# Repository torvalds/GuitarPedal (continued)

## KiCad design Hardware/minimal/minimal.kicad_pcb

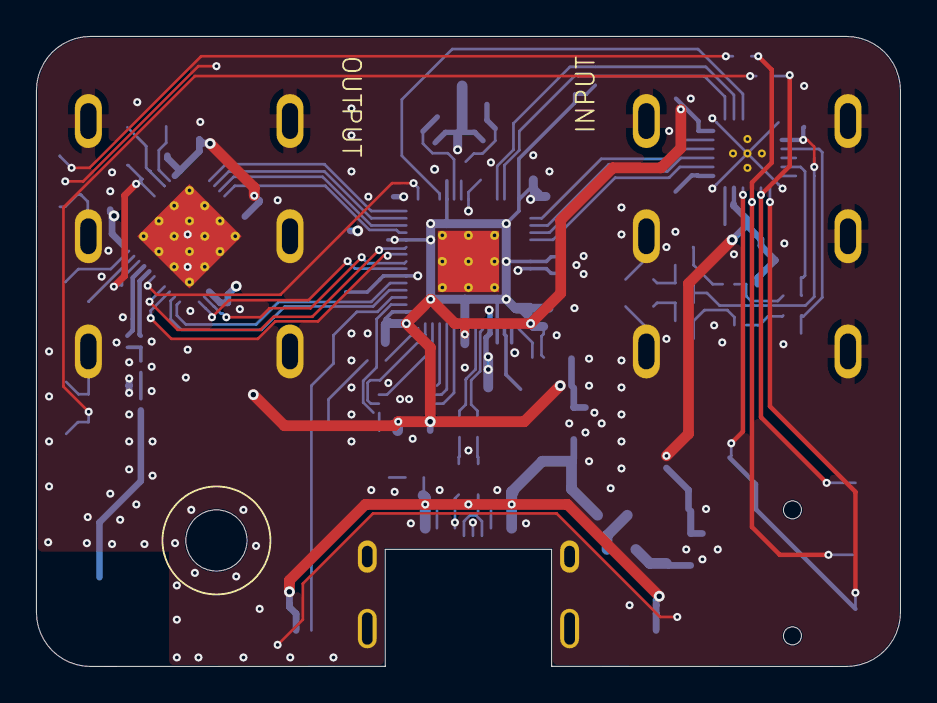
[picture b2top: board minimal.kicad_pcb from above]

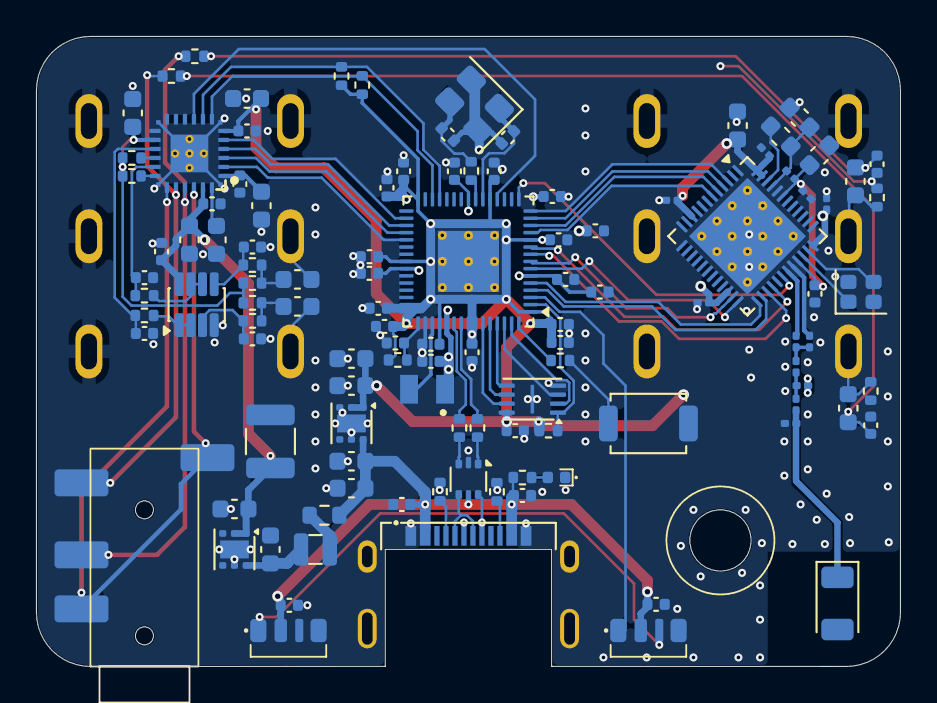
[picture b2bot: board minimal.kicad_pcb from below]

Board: 4 copper layers, 48.0 x 35.0 mm, 114 parts (112 on the bottom side), 80 nets.

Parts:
AE501: 2.4GHz; Johanson_2450AT18x100
C102, C103, C107, C108, C301, C320, C322, C323, C404, C405, C407, C408, C409, C410, C411, C412, C413, C415, C417: 0.1uF; C_0402_1005Metric
C104, C106, C109, C110, C111, C112, C303, C304, C305, C309, C318, C319, C509, C510: 2.2uF; C_0603_1608Metric
C105: 22uF; C_1210_3225Metric
C302, C308, C310, C311, C511: 2.2nF; C_0402_1005Metric
C306, C307: 150pF; C_0402_1005Metric
C316, C317, C321, C508: 10uF; C_0603_1608Metric
C401, C402, C403, C406, C414, C416, C418, C421, C422: 4.7uF; C_0402_1005Metric
C419, C420: 15pF; C_0402_1005Metric
C501: 1.5pF; C_0201_0603Metric
C502: 2.0pF; C_0201_0603Metric
C503: 0.3pF; C_0201_0603Metric
C504, C505, C506, C507: 0.1uF; C_0201_0603Metric
C512: 10nF; C_0201_0603Metric
D101: LED; LED_0402_1005Metric
D102, D103: WS2812B-4020-V6
FB501: 120Ω; L_0201_0603Metric
J101: USB_C_Receptacle_USB2.0_16P; TYPE-C-16P-CB1.6
J301, J302: AudioJack3_SwitchTR; NRJ6HM-1-PRE
J303: AudioJack4; PJ-320D
L101: 2.2uH; L_0806
L401: 3.3uH; AOTA-B2016
L501: 4.7uH; L_0603_1608Metric
L502: 2.7nH; L_0201_0603Metric
L503, L504: 3.5nH; L_0201_0603Metric
R101, R102, R105, R106: 5k1; R_0402_1005Metric
R103, R401, R403: 2.2kΩ; R_0402_1005Metric
R104: 1R; R_0603_1608Metric
R301, R307: 1k; R_0402_1005Metric
R302, R303, R304, R308: 1MEG; R_0402_1005Metric
R305, R306, R309, R310, R312, R313: 100R; R_0402_1005Metric
R402, R404, R405: 33Ω; R_0402_1005Metric
R406: 1kΩ; R_0402_1005Metric
SW101: SW_SPST; SW_SPST_TS-1088-xR020
U102: USBLC6-2P6; SOT-666
U103, U104: TLV76733DRVx; WSON-6-1EP_2x2mm_P0.65mm_EP1x1.6mm
U301: OPA2323; TSOT-23-8
U302: TAC5112; TAC5242
U401: APS6404L-3SQRx-ZR; Winbond_USON-8-1EP_3x2mm_P0.5mm_EP0.2x1.6mm
U402: RP2354A; QFN-60-1EP_7x7mm_P0.4mm_EP3.4x3.4mm_ThermalVias
U501: NRF54L10-QFAA-R7; QFN-48-1EP_6x6mm_P0.4mm_EP4.6x4.6mm_ThermalVias
Y401: ABM8-272-T3; Crystal_SMD_3225-4Pin_3.2x2.5mm
Y501: 32MHz; Crystal_SMD_2016-4Pin_2.0x1.6mm

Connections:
+1V1: C402.1, C403.1, C405.1, C407.1, C408.1, L401.1, U402.6 (DVDD), U402.23 (DVDD), U402.39 (DVDD), U402.50 (VREG_FB)
+3.3VA: C105.1, C109.1, C301.2, C321.1, C323.1, U103.1 (OUT), U103.2 (SNS), U301.8 (V+), U302.23 (AVDD)
+3V3: C111.1, C112.1, C316.1, C322.1, C401.1, C404.1, C409.1, C410.1, C411.1, C412.1, C413.1, C414.1, C415.1, C416.1, C417.1, C418.1, C421.1, C422.1, C504.1, C505.1, C506.1, C507.1, C508.1, R105.1, R106.1, R401.2, R402.1, U104.1 (OUT), U104.2 (SNS), U302.6 (IOVDD), U401.8 (VDD), U402.1 (IOVDD), U402.11 (IOVDD), U402.20 (IOVDD), U402.30 (IOVDD), U402.38 (IOVDD), U402.44 (ADC_AVDD), U402.45 (IOVDD), U402.49 (VREG_VIN), U402.53 (USB_OTP_VDD), U402.54 (QSPI_IOVDD), U501.10 (VDD), U501.22 (VDD), U501.36 (VDD), U501.47 (VDD), U501.48 (VDD)
/BOOTSEL: R403.1, SW101.2 (B)
/OUT1P: J303.T, R301.1, U302.20 (OUT1P)
/OUT2P: J303.R1, R307.1, U302.21 (OUT2P)
/RP2354/GPIO0: R401.1, U401.1 (~CE), U402.2 (GPIO0)
/RP2354/GPIO1: D102.1 (DIN), U402.3 (GPIO1)
/RP2354/GPIO2: U402.4 (GPIO2), U501.26 (SWDCLK)
/RP2354/GPIO3: U402.5 (GPIO3), U501.25 (SWDIO)
/RP2354/GPIO4: U402.7 (GPIO4), U501.24 (P0.01)
/RP2354/GPIO5: U402.8 (GPIO5), U501.23 (P0.00)
/RP2354/GPIO6: U402.9 (GPIO6), U501.27 (P0.02)
/RP2354/GPIO7: U402.10 (GPIO7), U501.28 (P0.03)
/RP2354/GPIO8: U402.12 (GPIO8), U501.6 (P1.05/AIN1)
/RP2354/GPIO9: U402.13 (GPIO9), U501.5 (P1.04/AIN0)
/RP2354/GPIO10: U402.14 (GPIO10), U501.4 (P1.03/NFC2/CK)
/RP2354/GPIO11: U402.15 (GPIO11), U501.3 (P1.02/NFC1)
/RP2354/GPIO12: U402.16 (GPIO12), U501.30 (nRESET)
/RP2354/GPIO15: U302.9 (GPIO1), U402.19 (GPIO15)
/RP2354/GPIO16: R106.2, U302.8 (SDA), U402.27 (GPIO16)
/RP2354/GPIO17: R105.2, U302.7 (SCL), U402.28 (GPIO17)
/RP2354/GPIO20: U302.5 (DIN), U402.32 (GPIO20)
/RP2354/GPIO21: U302.4 (DOUT), U402.33 (GPIO21)
/RP2354/GPIO22: U302.3 (FSYNC), U402.34 (GPIO22)
/RP2354/GPIO23: U302.2 (BCLK), U402.35 (GPIO23)
/RP2354/SCLK: U401.6 (SCLK), U402.56 (QSPI_SCLK)
/RP2354/SD0: U401.5 (SI/SIO0), U402.57 (QSPI_SD0)
/RP2354/SD1: U401.2 (SO/SIO1), U402.59 (QSPI_SD1)
/RP2354/SD2: U401.3 (SIO2), U402.58 (QSPI_SD2)
/RP2354/SD3: U401.7 (SIO3), U402.55 (QSPI_SD3)
/RP2354/VREG_AVDD: C406.1, R402.2, U402.46 (VREG_AVDD)
/RP2354/VREG_LX: L401.2, U402.48 (VREG_LX)
/RP2354/XIN: C419.1, U402.21 (XIN), Y401.1
/RP2354/XOUT: R406.1, U402.22 (XOUT)
/TAC5212/DREG: C317.1, C320.1, U302.1 (DREG)
/TAC5212/IN1M: R313.2, U302.16 (IN1M)
/TAC5212/IN1P: C310.2, R309.2, U302.15 (IN1P)
/TAC5212/IN2M: R312.2, U302.18 (IN2M)
/TAC5212/IN2P: C311.2, R310.2, U302.17 (IN2P)
/TAC5212/IN^{LEFT}: C303.1, J301.T
/TAC5212/IN^{RIGHT}: C304.1, J301.R
/TAC5212/MICBIAS: C319.1, R303.1, R304.2, R312.1, R313.1, U302.14 (MICBIAS)
/TAC5212/OUT1M: J303.R2, J303.S, U302.19 (OUT1M), U302.22 (OUT2M)
/TAC5212/OUT^{LEFT}: C305.2, J302.T, R302.1
/TAC5212/OUT^{RIGHT}: C309.2, J302.R, R308.1
/TAC5212/VREF: C318.1, U302.24 (VREF)
/USB-D+: R404.2, U102.1 (I/O1)
/USB-D-: R405.2, U102.3 (I/O2)
/USBCONN-D+: J101.A6 (D+), J101.B6 (D+), U102.6 (I/O1)
/USBCONN-D-: J101.A7 (D-), J101.B7 (D-), U102.4 (I/O2)
/nRF54L10/DECA: C510.1, C511.1, C512.1, FB501.2, U501.33 (DECRF), U501.43 (DECA)
/nRF54L10/DECD: C509.1, FB501.1, L501.1, U501.45 (DECD)
GND: C102.1, C103.1, C104.2, C105.2, C106.2, C107.1, C108.1, C109.2, C110.2, C111.2, C112.2, C301.1, C302.1, C306.2, C307.2, C308.1, C310.1, C311.1, C316.2, C317.2, C318.2, C319.2, C320.2, C321.2, C322.2, C323.2, C401.2, C402.2, C403.2, C404.2, C405.2, C406.2, C407.2, C408.2, C409.2, C410.2, C411.2, C412.2, C413.2, C414.2, C415.2, C416.2, C417.2, C418.2, C419.2, C420.2, C421.2, C422.2, C501.2, C502.2, C503.2, C504.2, C505.2, C506.2, C507.2, C508.2, C509.2, C510.2, C511.2, C512.2, D101.1 (K), D102.4 (VSS), D103.4 (VSS), J101.A1 (GND), J101.A12 (GND), J101.B1 (GND), J101.B12 (GND), J101.SH (SHIELD), J301.RN, J301.S, J301.TN, J302.S, R101.2, R102.2, R302.2, R308.2, SW101.1 (A), U102.2 (GND), U103.3 (GND), U103.5 (GND), U103.7 (PAD), U104.3 (GND), U104.5 (GND), U104.7 (PAD), U301.4 (V-), U302.13 (ADDR), U302.A1 (GND), U302.A2 (GND), U302.A3 (GND), U302.A4 (GND), U302.PAD (GND), U401.4 (VSS), U401.9 (EPAD), U402.47 (VREG_PGND), U402.61 (GND), U501.32 (VSS_PA), U501.44 (VSS), U501.49 (VSS/PAD), Y401.2 (G), Y401.4 (G), Y501.2 (G), Y501.4 (G)
unnamed: AE501.1 (FEED_1), C503.1, L504.1
unnamed: C302.2, C305.1, R301.2
unnamed: C303.2, R303.2, R305.1
unnamed: C304.2, R304.1, R306.1
unnamed: C308.2, C309.1, R307.2
unnamed: C420.1, R406.2, Y401.3
unnamed: C501.1, L502.1, L503.2
unnamed: C502.1, L503.1, L504.2
unnamed: D101.2 (A), R103.1
unnamed: D102.3 (DOUT), D103.1 (DIN)
unnamed: J101.A5 (CC1), R101.1
unnamed: J101.B5 (CC2), R102.1
unnamed: L101.1, R104.2
unnamed: C106.1, L101.2, U103.6 (IN)
unnamed: C306.1, R305.2, U301.3 (+)
unnamed: R309.1, U301.1, U301.2 (-)
unnamed: C307.1, R306.2, U301.5 (+)
unnamed: R310.1, U301.6 (-), U301.7
unnamed: R403.2, U402.60 (QSPI_SS)
unnamed: R405.1, U402.51 (USB_DM)
unnamed: R404.1, U402.52 (USB_DP)
unnamed: L502.2, U501.31 (ANT)
unnamed: L501.2, U501.46 (DCC)
unnamed: U501.34 (XC1), Y501.1
unnamed: U501.35 (XC2), Y501.3
VBUS: C102.2, C103.2, C104.1, C107.2, C108.2, C110.1, D102.2 (VDD), D103.2 (VDD), J101.A4 (VBUS), J101.A9 (VBUS), J101.B4 (VBUS), J101.B9 (VBUS), R103.2, R104.1, U102.5 (VBUS), U104.6 (IN)

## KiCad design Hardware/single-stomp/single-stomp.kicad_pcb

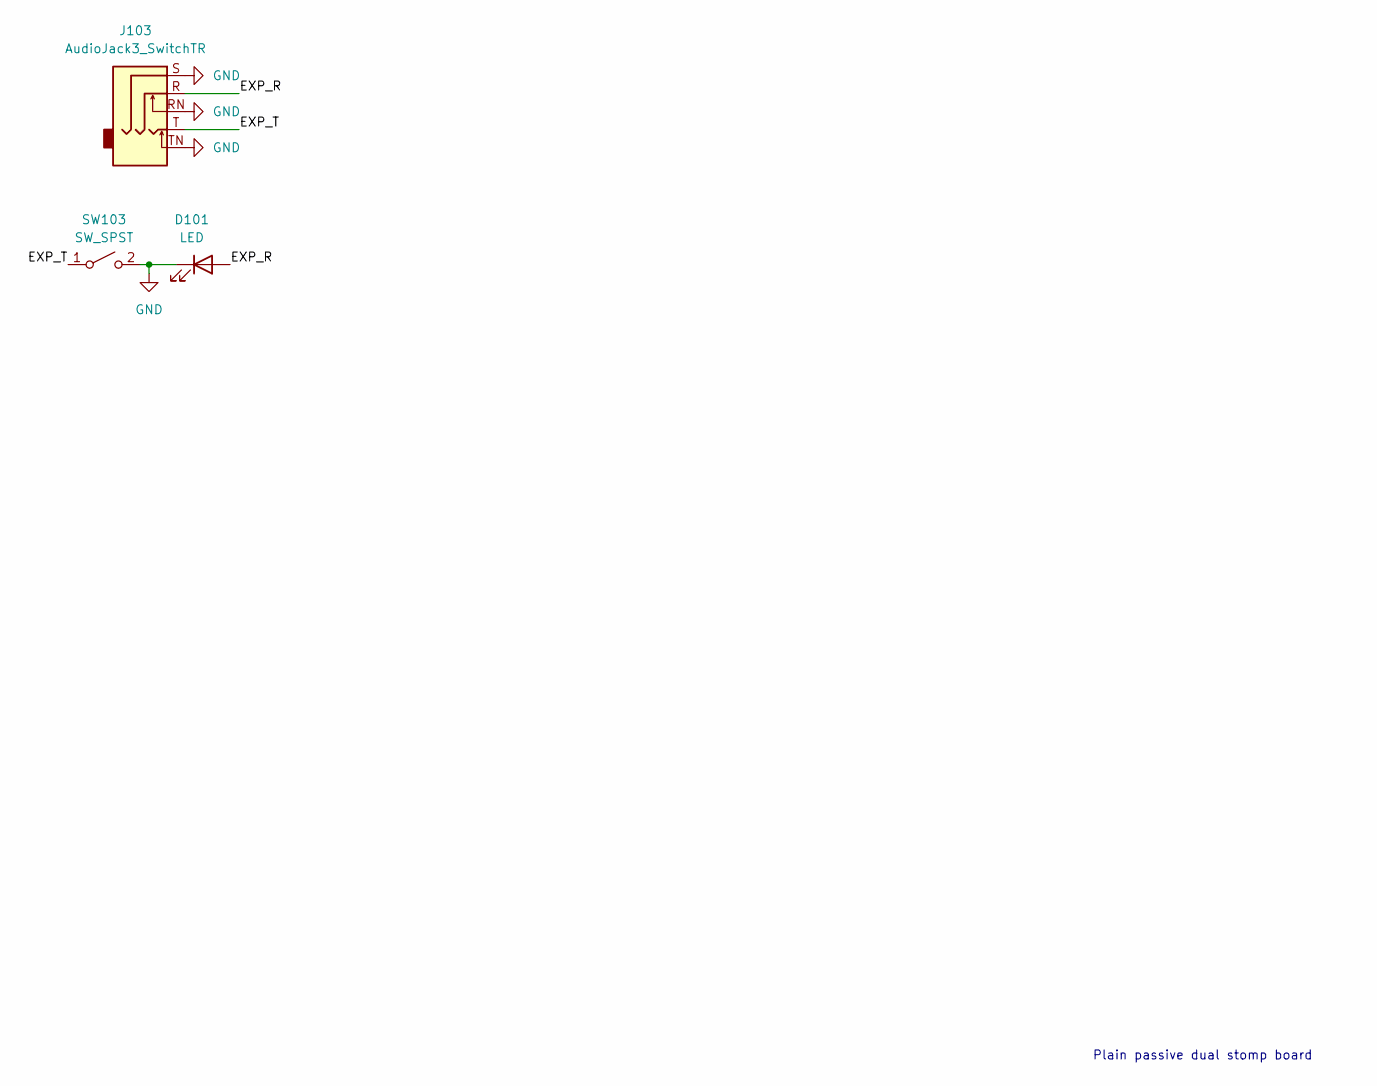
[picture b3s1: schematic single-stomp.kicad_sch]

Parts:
D101: LED; LED_D5.0mm
J103: AudioJack3_SwitchTR; NRJ6HM-1-PRE
SW103: SW_SPST; Daier PBS-24B-2

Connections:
/EXP_R: D101.2 (A), J103.R
/EXP_T: J103.T, SW103.1 (A)
GND: D101.1 (K), J103.RN, J103.S, J103.TN, SW103.2 (B)

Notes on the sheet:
Plain passive dual stomp board

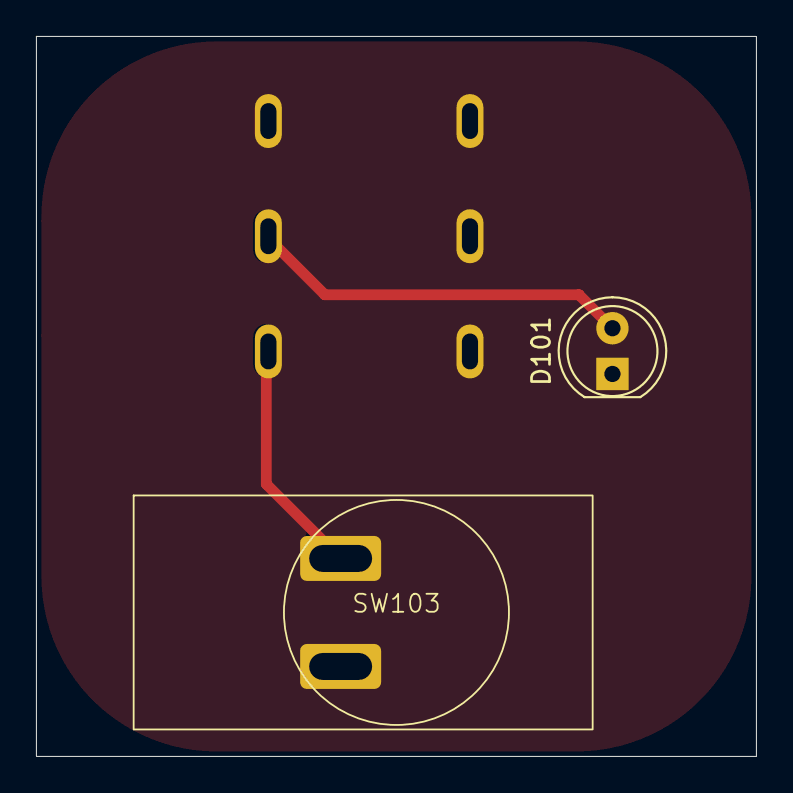
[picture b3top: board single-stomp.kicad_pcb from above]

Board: 2 copper layers, 40.0 x 40.0 mm, 3 parts (0 on the bottom side), 3 nets.

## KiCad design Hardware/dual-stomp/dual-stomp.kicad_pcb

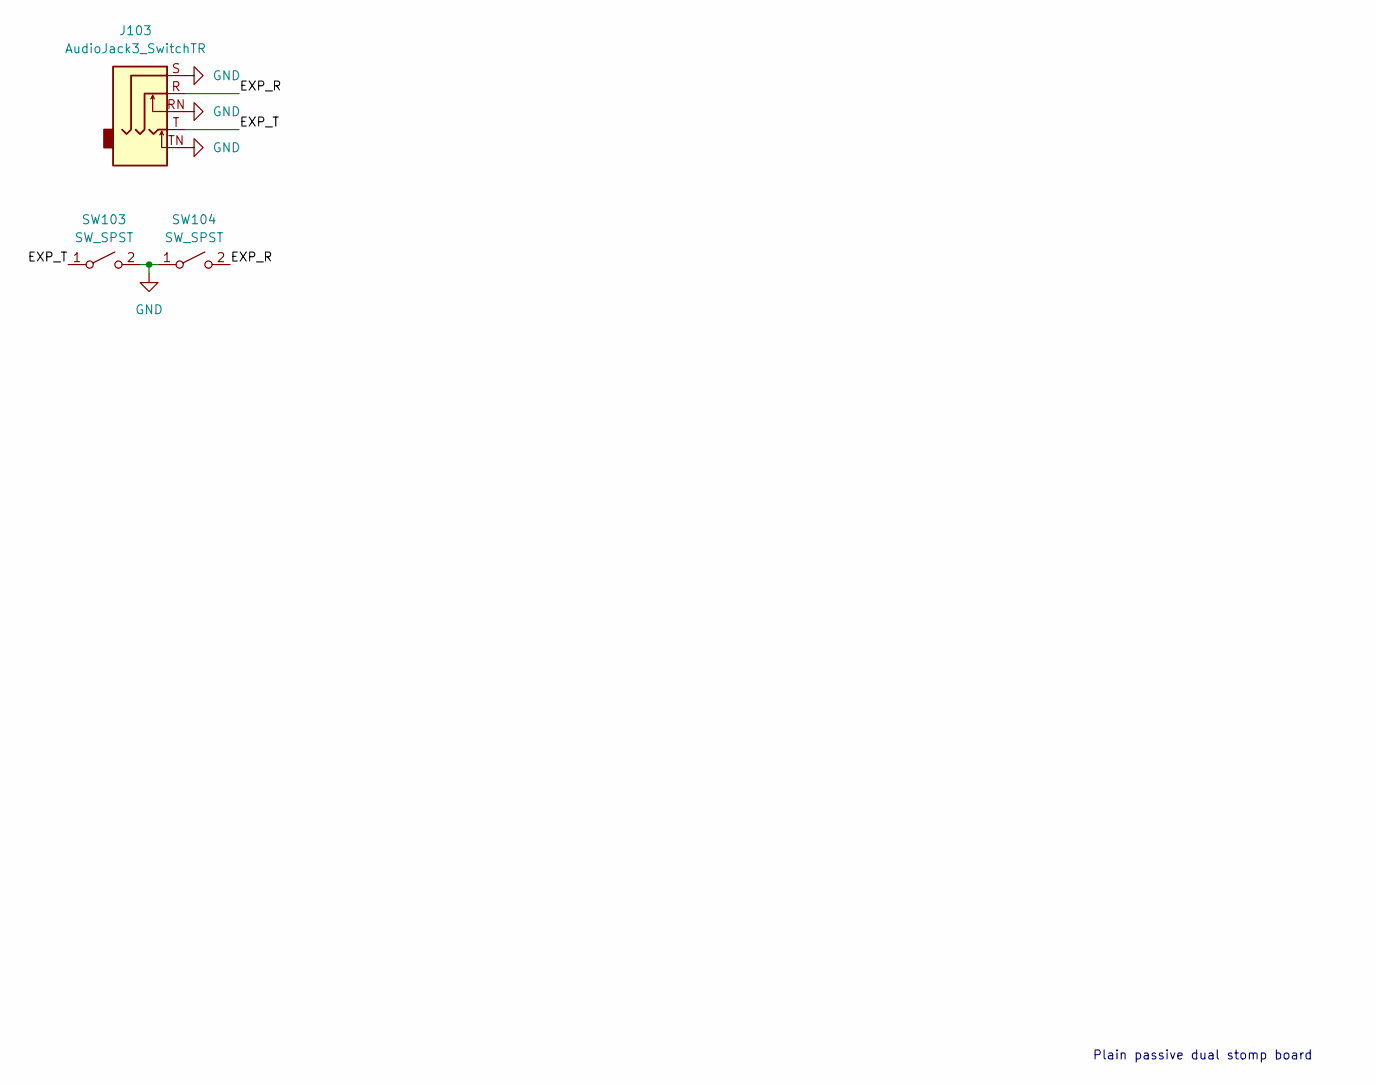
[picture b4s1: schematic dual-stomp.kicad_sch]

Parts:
J103: AudioJack3_SwitchTR; NRJ6HM-1-PRE
SW103, SW104: SW_SPST; Daier PBS-24B-2

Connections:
/EXP_R: J103.R, SW104.2 (B)
/EXP_T: J103.T, SW103.1 (A)
GND: J103.RN, J103.S, J103.TN, SW103.2 (B), SW104.1 (A)

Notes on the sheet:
Plain passive dual stomp board

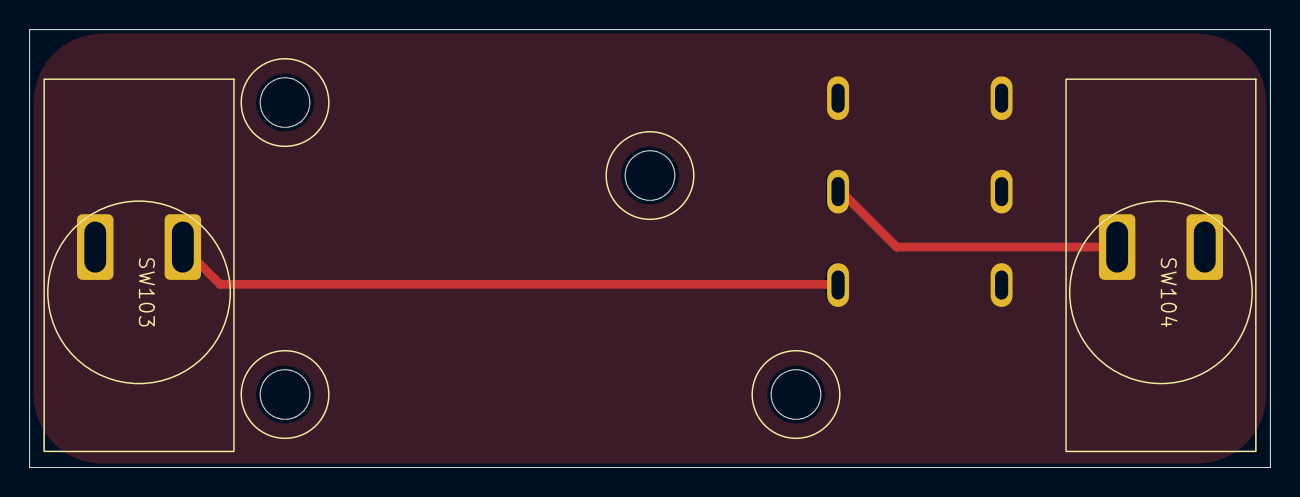
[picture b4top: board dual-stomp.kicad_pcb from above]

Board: 2 copper layers, 85.0 x 30.0 mm, 3 parts (0 on the bottom side), 3 nets.

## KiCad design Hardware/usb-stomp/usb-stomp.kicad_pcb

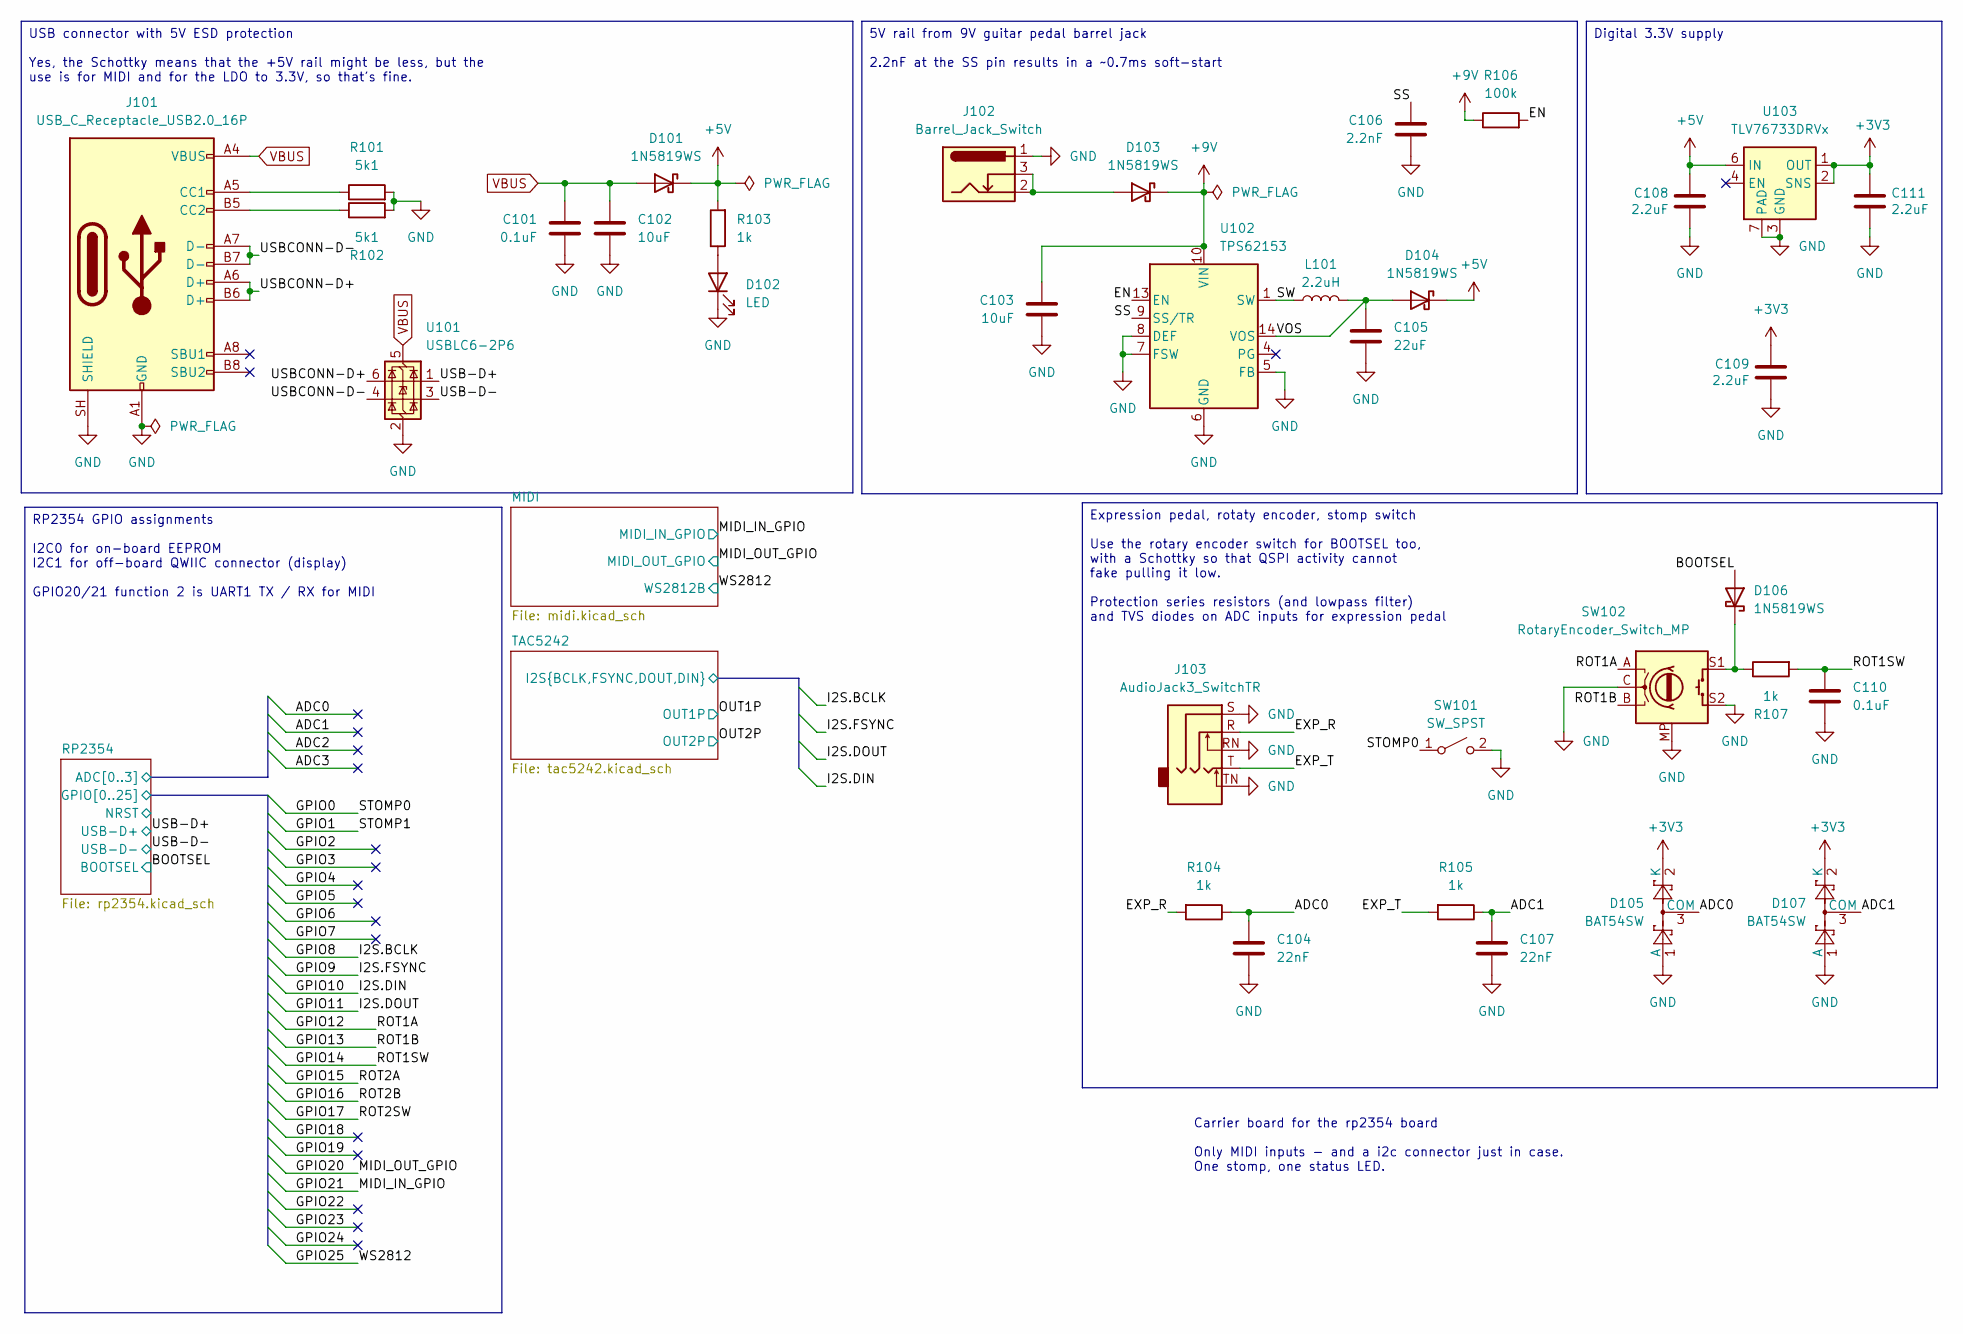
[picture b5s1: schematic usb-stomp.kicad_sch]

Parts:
C101, C110: 0.1uF; C_0402_1005Metric; MANUFACTURER_PART_NUMBER CL05B104KO5NNNC; LCSC PN C1525
C102, C103: 10uF; C_0603_1608Metric; MANUFACTURER_PART_NUMBER GRM188R61E106MA73D; LCSC PN C91606
C104, C107: 22nF; C_0402_1005Metric; MANUFACTURER_PART_NUMBER 0402B223K500NT; LCSC PN C1532
C105: 22uF; C_1210_3225Metric; MANUFACTURER_PART_NUMBER CL32B226KAJNNNE; LCSC PN C309062
C106: 2.2nF; C_0402_1005Metric; MANUFACTURER_PART_NUMBER GRM1555C1H222GA01D; LCSC PN C2987940
C108, C109, C111: 2.2uF; C_0603_1608Metric; MANUFACTURER_PART_NUMBER GRM188Z71E225KE43D; LCSC PN C415535
D101, D103, D104, D106: 1N5819WS; D_SOD-323; MANUFACTURER_PART_NUMBER 1N5819WS; LCSC PN C191023
D102: LED; LED_0402_1005Metric; MANUFACTURER_PART_NUMBER LTST-C281KGKT; LCSC PN C160479
D105, D107: BAT54SW; SOT-323_SC-70; MANUFACTURER_PART_NUMBER BAT54SW; LCSC PN C22466373
J101: USB_C_Receptacle_USB2.0_16P; USB_C_Receptacle_GCT_USB4105-xx-A_16P_TopMnt_Horizontal; MANUFACTURER_PART_NUMBER GT-USB-7010C; LCSC PN C2843967
J102: Barrel_Jack_Switch; Wurth WR-DC 2.1mm Power Jack
J103: AudioJack3_SwitchTR; NRJ6HM-1-PRE
L101: 2.2uH; L_0806; MANUFACTURER_PART_NUMBER DFE201612E-2R2M=P2; LCSC PN C337893
R101, R102: 5k1; R_0402_1005Metric; MANUFACTURER_PART_NUMBER 0402WGF5101TCE; LCSC PN C25905
R103, R104, R105, R107: 1k; R_0402_1005Metric; MANUFACTURER_PART_NUMBER RT0402FRE071KL; LCSC PN C136974
R106: 100k; R_0402_1005Metric; MANUFACTURER_PART_NUMBER 0402WGF1003TCE; LCSC PN C25741
SW101: SW_SPST; Daier PBS-24B-2
SW102: RotaryEncoder_Switch_MP; RotaryEncoder_Alps_EC11E-Switch_Vertical_H20mm
U101: USBLC6-2P6; SOT-666; MANUFACTURER_PART_NUMBER USBLC6-2P6; LCSC PN C15999
U102: TPS62153; VQFN-16-1EP_3x3mm_P0.5mm_EP1.68x1.68mm_ThermalVias; MANUFACTURER_PART_NUMBER TPS62153RGTR; LCSC PN C477927
U103: TLV76733DRVx; WSON-6-1EP_2x2mm_P0.65mm_EP1x1.6mm; MANUFACTURER_PART_NUMBER TLV76733DRVR; LCSC PN C2848334

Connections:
+3V3: C109.1, C111.1, D105.2 (K), D107.2 (K), U103.1 (OUT), U103.2 (SNS); also elsewhere on the board
+5V: C108.1, D101.1 (K), D104.1 (K), R103.2, U103.6 (IN); also elsewhere on the board
+9V: C103.1, D103.1 (K), R106.1, U102.10 (VIN), U102.11 (VIN), U102.12 (VIN)
/BOOTSEL: D106.2 (A); also elsewhere on the board
/EN: R106.2, U102.13 (EN)
/EXP_R: J103.R, R104.2
/EXP_T: J103.T, R105.2
/RP2354/ADC0: C104.1, D105.3 (COM), R104.1; also elsewhere on the board
/RP2354/ADC1: C107.1, D107.3 (COM), R105.1; also elsewhere on the board
/RP2354/GPIO0: SW101.1 (A); also elsewhere on the board
/RP2354/GPIO12: SW102.A; also elsewhere on the board
/RP2354/GPIO13: SW102.B; also elsewhere on the board
/RP2354/GPIO14: C110.2, R107.2; also elsewhere on the board
/SS: C106.2, U102.9 (SS/TR)
/SW: L101.1, U102.1 (SW), U102.2 (SW), U102.3 (SW)
/USB-D+: U101.1 (I/O1); also elsewhere on the board
/USB-D-: U101.3 (I/O2); also elsewhere on the board
/USBCONN-D+: J101.A6 (D+), J101.B6 (D+), U101.6 (I/O1)
/USBCONN-D-: J101.A7 (D-), J101.B7 (D-), U101.4 (I/O2)
/VOS: C105.1, D104.2 (A), L101.2, U102.14 (VOS)
GND: C101.1, C102.2, C103.2, C104.2, C105.2, C106.1, C107.2, C108.2, C109.2, C110.1, C111.2, D102.1 (K), D105.1 (A), D107.1 (A), J101.A1 (GND), J101.A12 (GND), J101.B1 (GND), J101.B12 (GND), J101.SH (SHIELD), J102.1, J103.RN, J103.S, J103.TN, R101.2, R102.2, SW101.2 (B), SW102.C, SW102.MP, SW102.S2, U101.2 (GND), U102.5 (FB), U102.6 (GND), U102.7 (FSW), U102.8 (DEF), U102.15 (GND), U102.16 (GND), U102.17 (GND), U103.3 (GND), U103.5 (GND), U103.7 (PAD); also elsewhere on the board
unnamed: D102.2 (A), R103.1
unnamed: D103.2 (A), J102.2, J102.3
unnamed: D106.1 (K), R107.1, SW102.S1
unnamed: J101.A5 (CC1), R101.1
unnamed: J101.B5 (CC2), R102.1
VBUS: C101.2, C102.1, D101.2 (A), J101.A4 (VBUS), J101.A9 (VBUS), J101.B4 (VBUS), J101.B9 (VBUS), U101.5 (VBUS)

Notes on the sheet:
Carrier board for the rp2354 board Only MIDI inputs - and a i2c connector just in case. One stomp, one status LED.
Expression pedal, rotaty encoder, stomp switch Use the rotary encoder switch for BOOTSEL too, with a Schottky so that QSPI activity cannot fake pulling it low. Protection series resistors (and lowpass filter) and TVS diodes on ADC inputs for expression pedal
5V rail from 9V guitar pedal barrel jack 2.2nF at the SS pin results in a ~0.7ms soft-start
RP2354 GPIO assignments I2C0 for on-board EEPROM I2C1 for off-board QWIIC connector (display) GPIO20/21 function 2 is UART1 TX / RX for MIDI
Digital 3.3V supply
USB connector with 5V ESD protection Yes, the Schottky means that the +5V rail might be less, but the use is for MIDI and for the LDO to 3.3V, so that's fine.

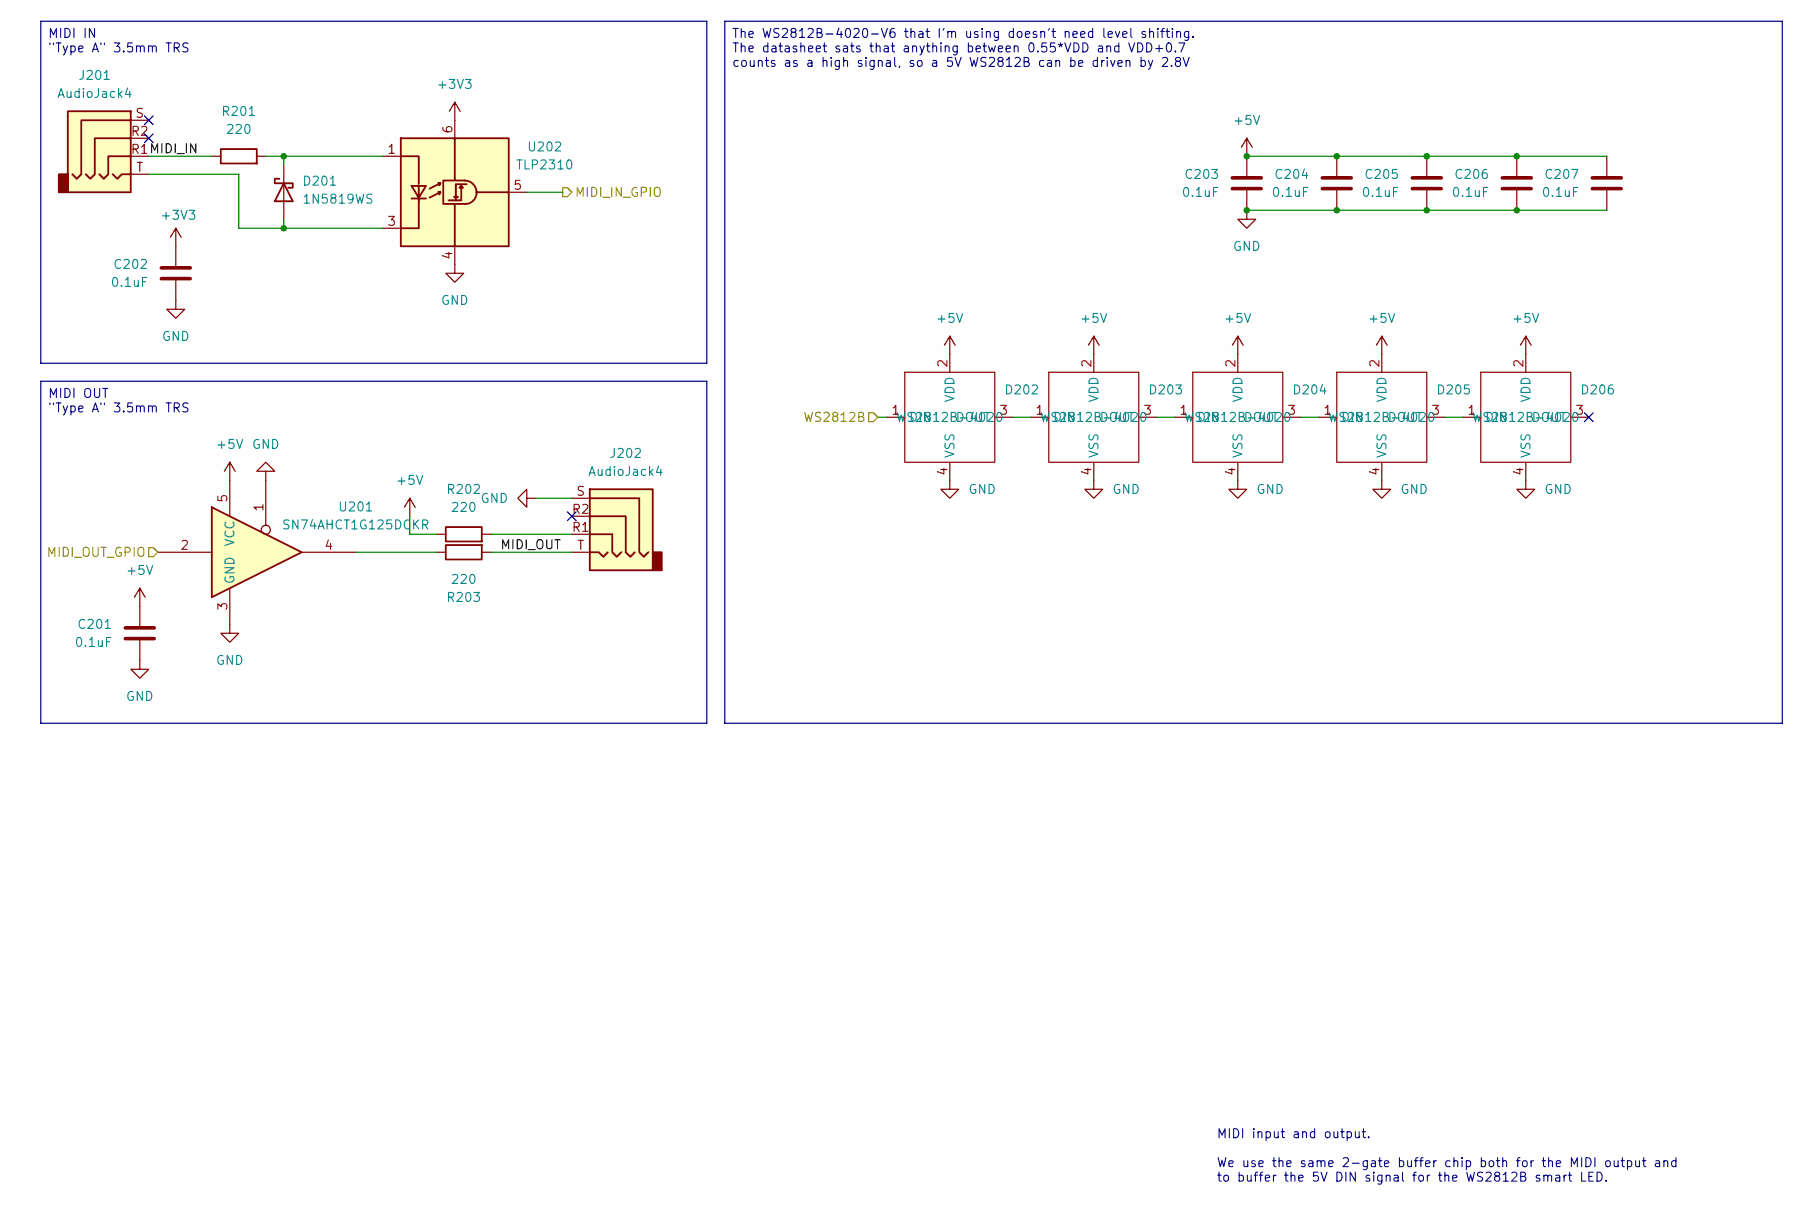
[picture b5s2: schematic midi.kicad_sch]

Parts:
C201, C202, C203, C204, C205, C206, C207: 0.1uF; C_0402_1005Metric; MANUFACTURER_PART_NUMBER CL05B104KO5NNNC; LCSC PN C1525
D201: 1N5819WS; D_SOD-323; MANUFACTURER_PART_NUMBER 1N5819WS; LCSC PN C191023
D202, D203, D204, D205, D206: WS2812B-4020; MANUFACTURER_PART_NUMBER WS2812B-4020; LCSC PN C965557
J201, J202: AudioJack4; PJ-320D; MANUFACTURER_PART_NUMBER PJ-320D; LCSC PN C431535
R201, R202, R203: 220; R_0402_1005Metric; MANUFACTURER_PART_NUMBER 0402WGF2200TCE; LCSC PN C25091
U201: SN74AHCT1G125DCKR; SOT-353_SC-70-5; MANUFACTURER_PART_NUMBER SN74AHCT1G125DCKR; LCSC PN C350557
U202: TLP2310; SO-5-6_4.55x3.7mm_P1.27mm; MANUFACTURER_PART_NUMBER TLP2310; LCSC PN C7473281

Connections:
+3V3: C202.2, U202.6 (VDD); also elsewhere on the board
+5V: C201.2, C203.2, C204.2, C205.2, C206.2, C207.2, D202.2 (VDD), D203.2 (VDD), D204.2 (VDD), D205.2 (VDD), D206.2 (VDD), R202.1, U201.5 (VCC); also elsewhere on the board
/MIDI/MIDI_IN: J201.R1, R201.1
/MIDI/MIDI_OUT: J202.T, R203.2
/RP2354/GPIO20: U201.2; also elsewhere on the board
/RP2354/GPIO21: U202.5 (VO); also elsewhere on the board
/RP2354/GPIO25: D202.1 (DIN); also elsewhere on the board
GND: C201.1, C202.1, C203.1, C204.1, C205.1, C206.1, C207.1, D202.4 (VSS), D203.4 (VSS), D204.4 (VSS), D205.4 (VSS), D206.4 (VSS), J202.S, U201.1, U201.3 (GND), U202.4 (GND); also elsewhere on the board
unnamed: D201.2 (A), J201.T, U202.3 (K)
unnamed: D201.1 (K), R201.2, U202.1 (A)
unnamed: D202.3 (DOUT), D203.1 (DIN)
unnamed: D203.3 (DOUT), D204.1 (DIN)
unnamed: D204.3 (DOUT), D205.1 (DIN)
unnamed: D205.3 (DOUT), D206.1 (DIN)
unnamed: J202.R1, R202.2
unnamed: R203.1, U201.4

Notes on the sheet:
MIDI input and output. We use the same 2-gate buffer chip both for the MIDI output and to buffer the 5V DIN signal for the WS2812B smart LED.
MIDI IN "Type A" 3.5mm TRS
MIDI OUT "Type A" 3.5mm TRS
The WS2812B-4020-V6 that I'm using doesn't need level shifting. The datasheet sats that anything between 0.55*VDD and VDD+0.7 counts as a high signal, so a 5V WS2812B can be driven by 2.8V
